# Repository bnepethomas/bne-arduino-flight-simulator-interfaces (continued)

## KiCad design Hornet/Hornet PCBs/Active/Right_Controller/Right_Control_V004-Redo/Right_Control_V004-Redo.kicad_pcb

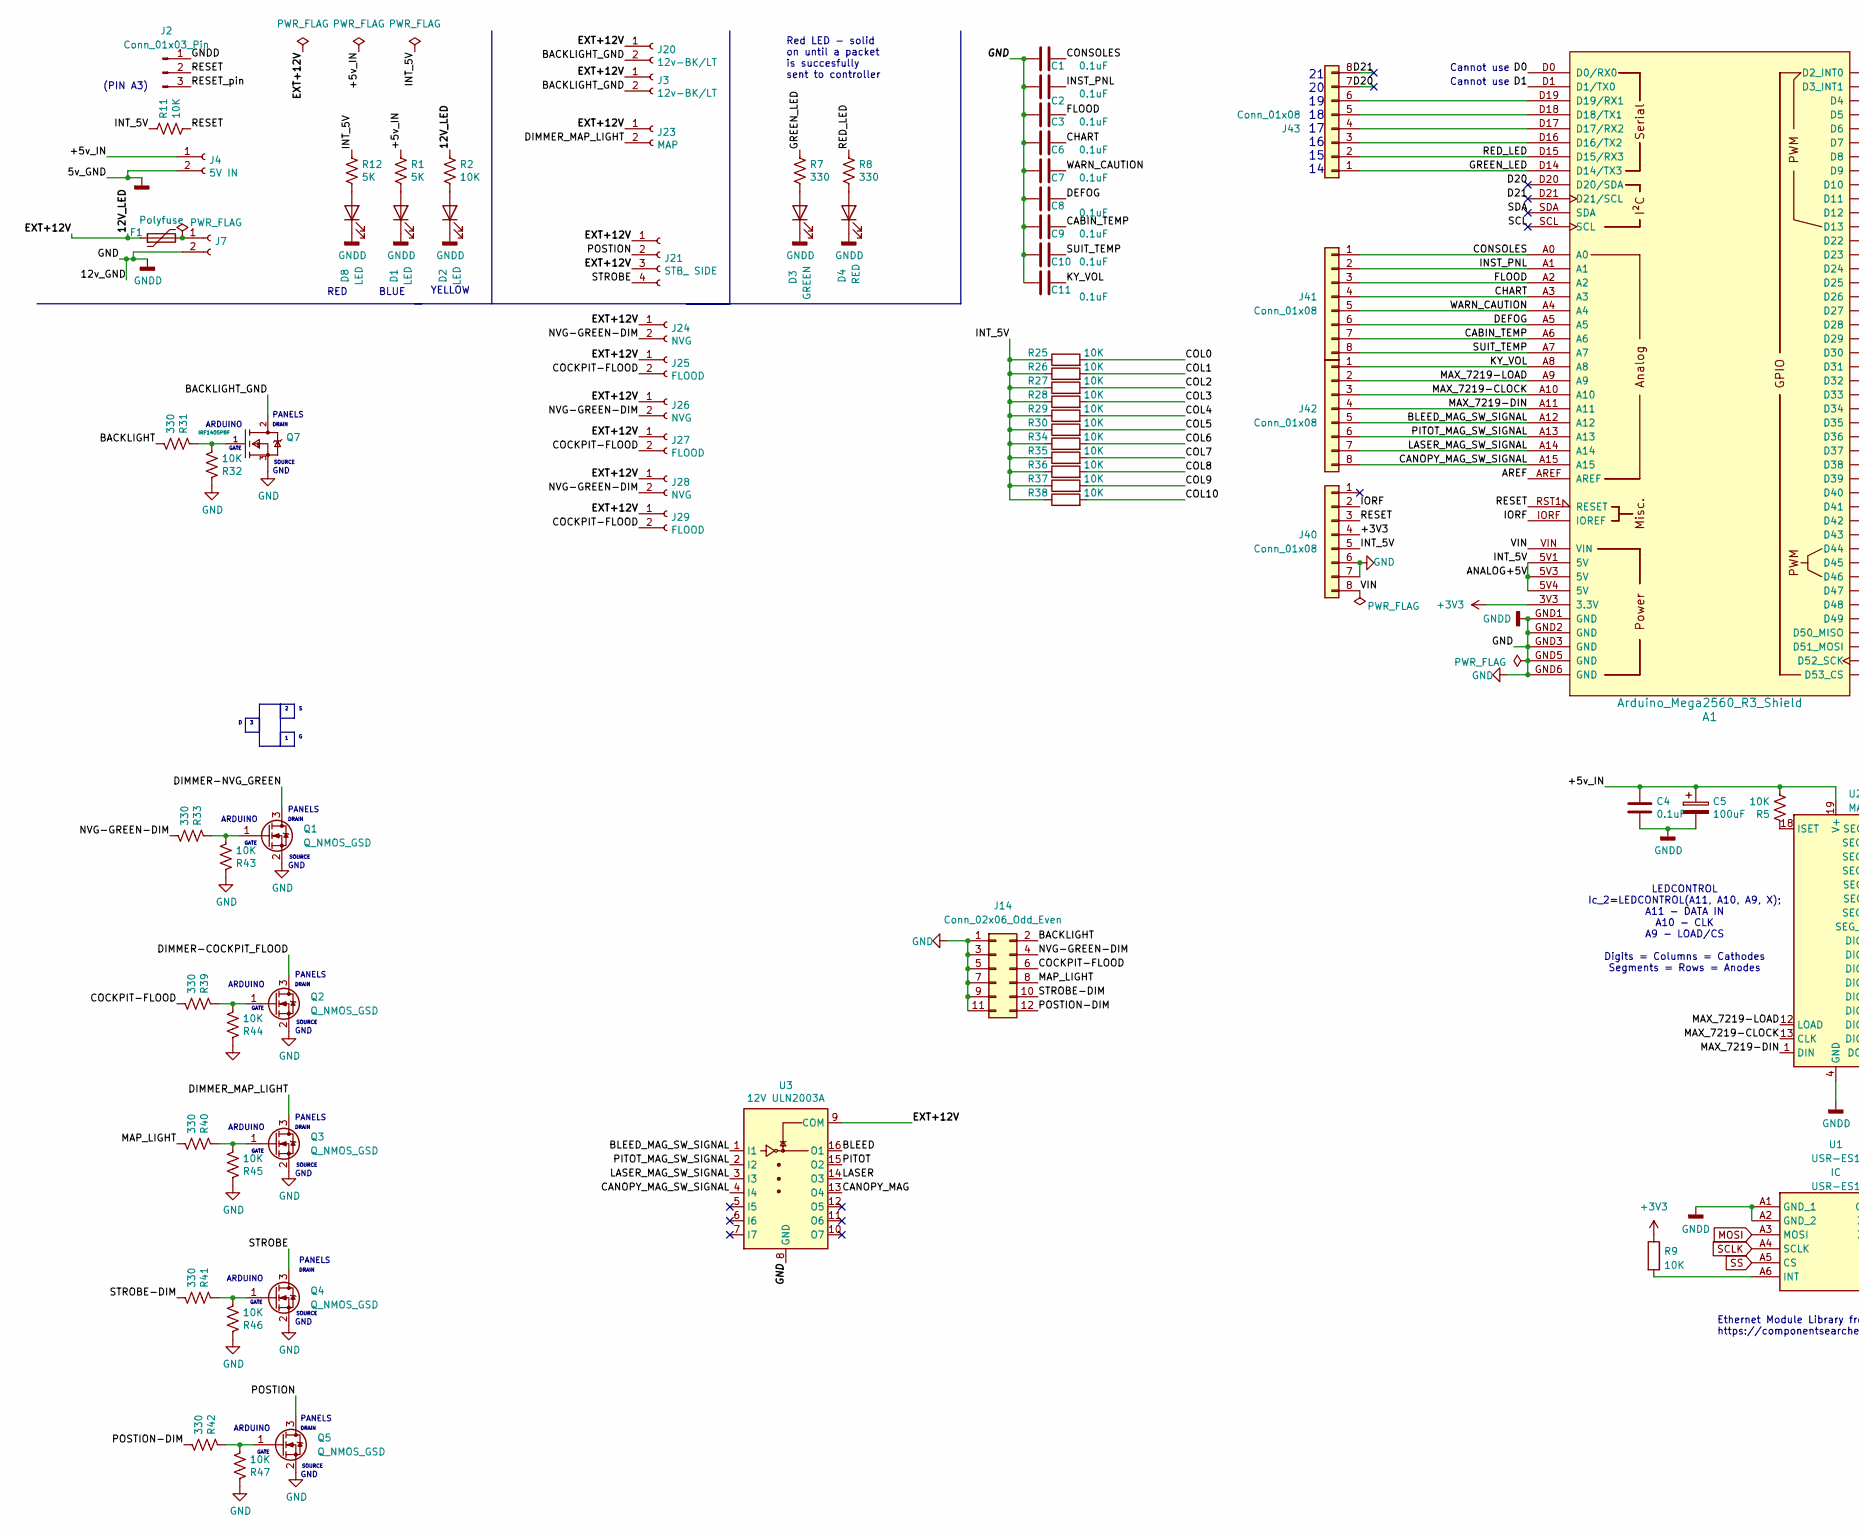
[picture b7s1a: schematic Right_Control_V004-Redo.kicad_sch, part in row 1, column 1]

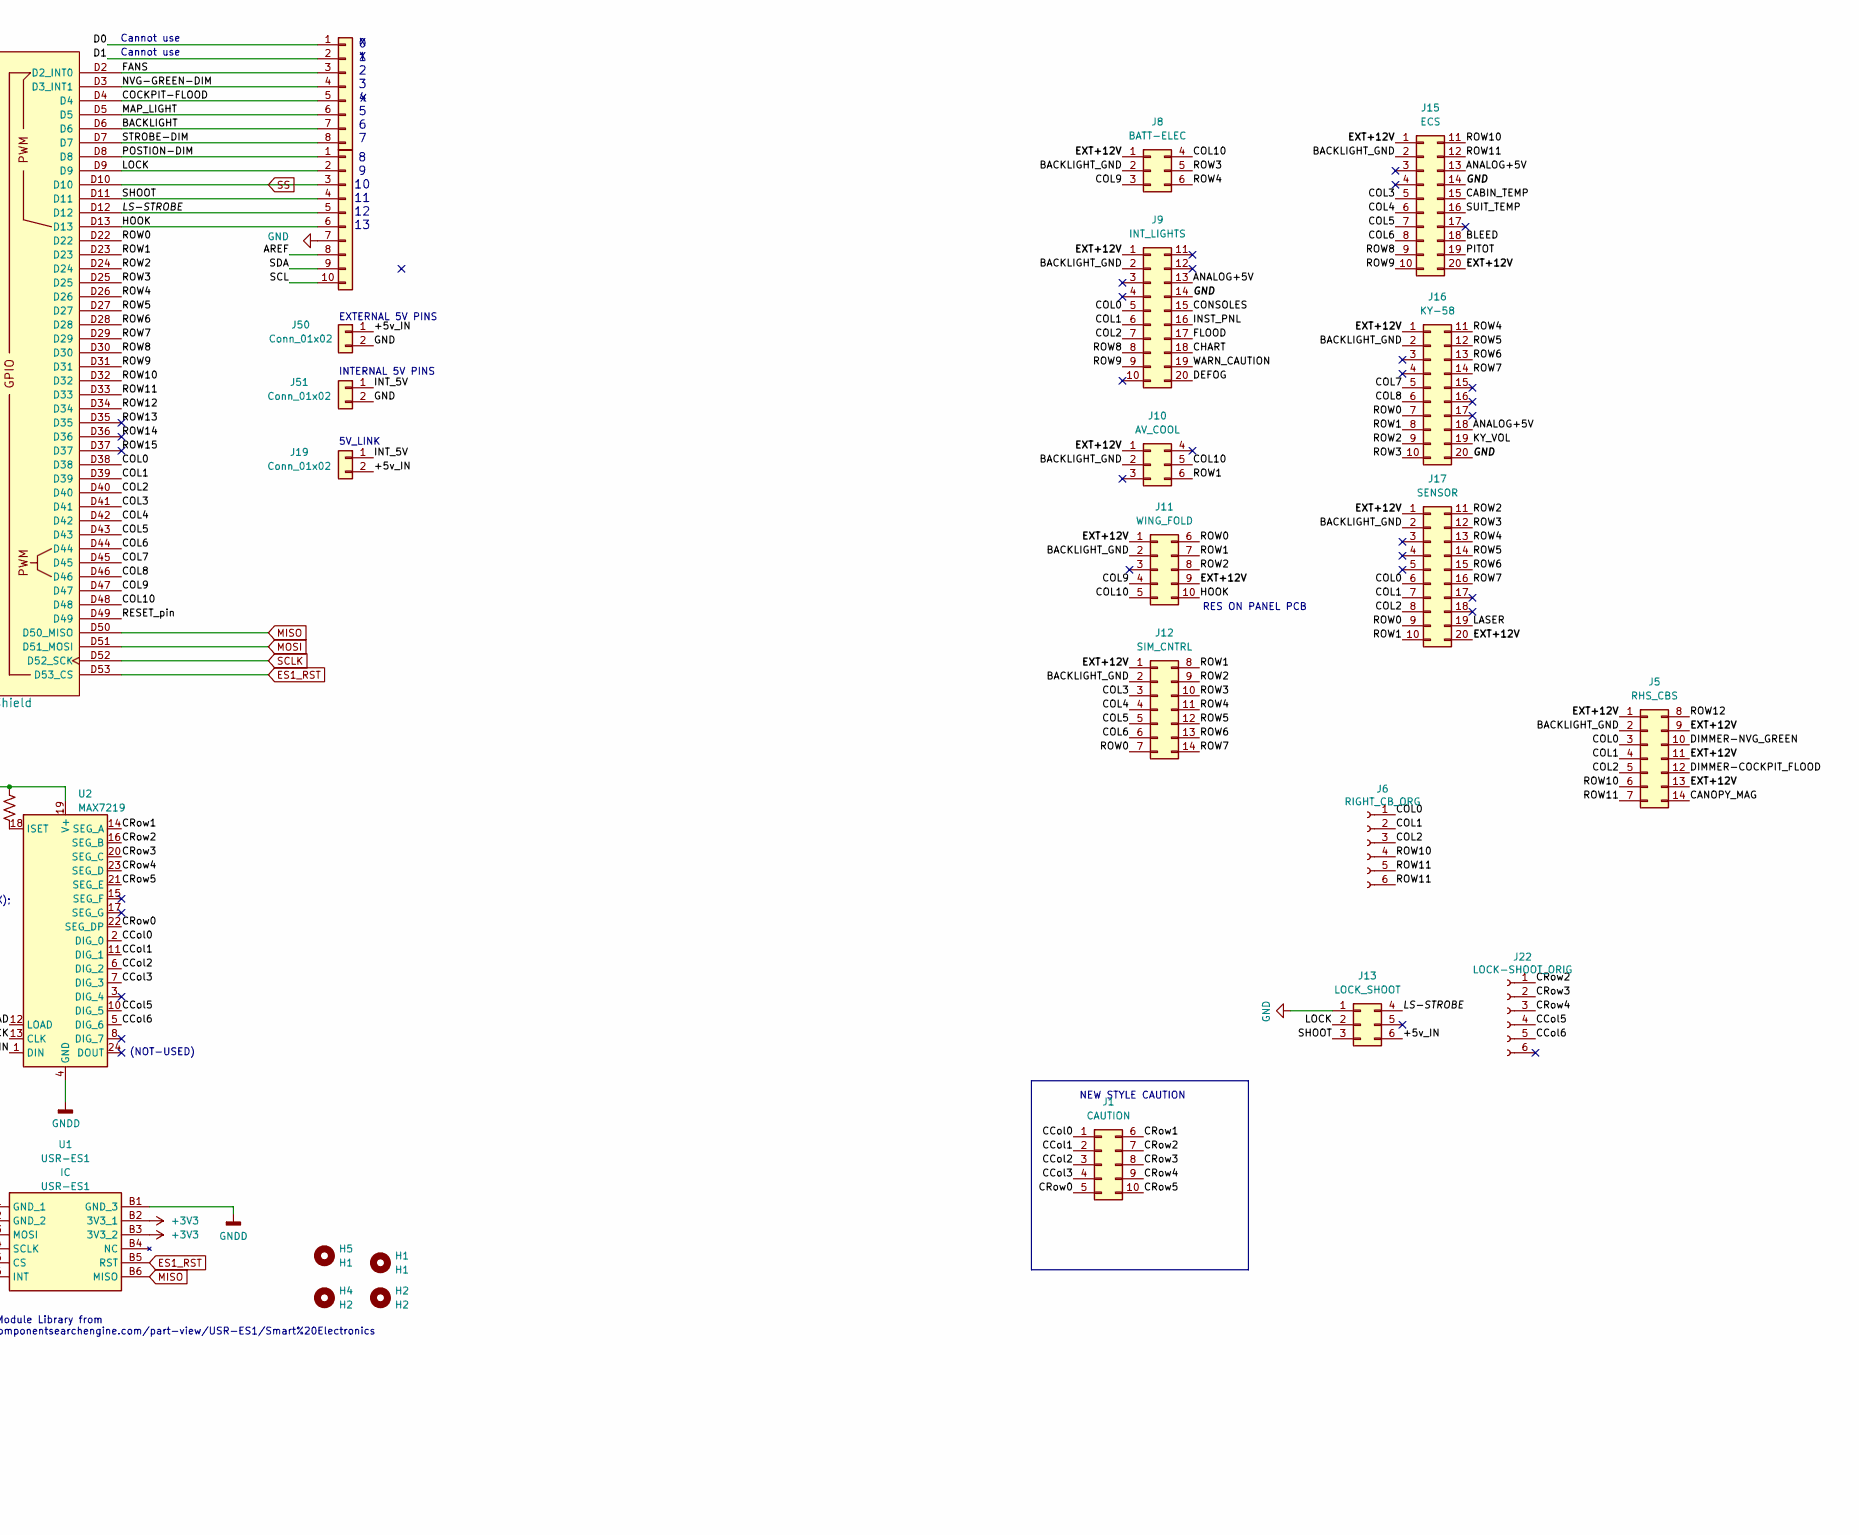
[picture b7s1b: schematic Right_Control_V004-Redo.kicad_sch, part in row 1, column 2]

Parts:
A1: Arduino_Mega2560_R3_Shield
C1, C2, C3, C4, C6, C7, C8, C9, C10, C11: 0.1uF; C_0805_2012Metric
C5: 100uF; C_1210_3225Metric
D1, D2, D8: LED; LED_0805_2012Metric
D3: GREEN; LED_0805_2012Metric
D4: RED; LED_0805_2012Metric
F1: Polyfuse; Fuse_1206_3216Metric
H1, H5: H1; MountingHole_2.5mm
H2, H4: H2; MountingHole_2.5mm
J1: CAUTION; IDC-Header_2x05_P2.54mm_Vertical
J2: Conn_01x03_Pin; PinHeader_1x03_P2.54mm_Vertical
J3, J20: 12v-BK/LT; Molex_KK-254_AE-6410-02A_1x02_P2.54mm_Vertical
J4: 5V IN; BarrelJack_Horizontal
J5: RHS_CBS; IDC-Header_2x07_P2.54mm_Vertical
J6: RIGHT_CB_ORG; Molex_KK-254_AE-6410-06A_1x06_P2.54mm_Vertical
J7: STEPPER IN 12-20VDC; BarrelJack_Horizontal
J8: BATT-ELEC; IDC-Header_2x03_P2.54mm_Vertical
J9: INT_LIGHTS; IDC-Header_2x10_P2.54mm_Vertical
J10: AV_COOL; IDC-Header_2x03_P2.54mm_Vertical
J11: WING_FOLD; IDC-Header_2x05_P2.54mm_Vertical
J12: SIM_CNTRL; IDC-Header_2x07_P2.54mm_Vertical
J13: LOCK_SHOOT; IDC-Header_2x03_P2.54mm_Vertical
J14: Conn_02x06_Odd_Even; PinHeader_2x06_P2.54mm_Vertical
J15: ECS; IDC-Header_2x10_P2.54mm_Vertical
J16: KY-58; IDC-Header_2x10_P2.54mm_Vertical
J17: SENSOR; IDC-Header_2x10_P2.54mm_Vertical
J19, J50, J51: Conn_01x02; PinHeader_1x02_P2.54mm_Vertical
J21: STB_ SIDE; Molex_KK-254_AE-6410-04A_1x04_P2.54mm_Vertical
J22: LOCK-SHOOT_ORIG; Molex_KK-254_AE-6410-06A_1x06_P2.54mm_Vertical
J23: MAP; Molex_KK-254_AE-6410-02A_1x02_P2.54mm_Vertical
J24, J26, J28: NVG; Molex_KK-254_AE-6410-02A_1x02_P2.54mm_Vertical
J25, J27, J29: FLOOD; Molex_KK-254_AE-6410-02A_1x02_P2.54mm_Vertical
J40, J41, J42, J43, J44: Conn_01x08; PinHeader_1x08_P2.54mm_Vertical
J45: Conn_01x10; PinHeader_1x10_P2.54mm_Vertical
Q1, Q2, Q3, Q4, Q5: Q_NMOS_GSD; SOT-23
Q7: IRF1405PBF; TO-220-3_Vertical; mouser part number 942-IRF1405PBF; digikey description MOSFET N-CH 55V 169A TO-220AB
R1, R12: 5K; R_0805_2012Metric
R2, R5, R9, R11, R25, R26, R27, R28, R29, R30, R32, R34, R35, R36, R37, R38, R43, R44, R45, R46, R47: 10K; R_0805_2012Metric
R7, R8, R31, R33, R39, R40, R41, R42: 330; R_0805_2012Metric
U1: USR-ES1; USRES1; Manufacturer_Part_Number USR-ES1
U2: MAX7219; DIP-24_W7.62mm_LongPads
U3: 12V ULN2003A; DIP-16_W7.62mm

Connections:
+3V3: A1.3V3 (3.3V), J40.4, R9.1, U1.B2 (3V3_1), U1.B3 (3V3_2)
/12V_LED: F1.1, J3.1, J5.1, J5.9, J5.11, J5.13, J8.1, J9.1, J10.1, J11.1, J11.9, J12.1, J15.1, J15.20, J16.1, J17.1, J17.20, J20.1, J21.1, J21.3, J23.1, J24.1, J25.1, J26.1, J27.1, J28.1, J29.1, R2.1, U3.9 (COM)
/+5v_IN: C4.1, C5.1, J4.1, J13.6, J19.2, J50.1, R1.1, R5.2, U2.19 (V+)
/ANALOG+5V: A1.5V1 (5V), A1.5V3 (5V), A1.5V4 (5V), J9.13, J15.13, J16.18, J19.1, J40.5, J51.1, R11.1, R12.1, R25.1, R26.1, R27.1, R28.1, R29.1, R30.1, R34.1, R35.1, R36.1, R37.1, R38.1
/AREF: A1.AREF, J45.8
/BACKLIGHT: A1.D6, J14.2, J44.7, R31.2
/BACKLIGHT_GND: J3.2, J5.2, J8.2, J9.2, J10.2, J11.2, J12.2, J15.2, J16.2, J17.2, J20.2, Q7.2 (D)
/BLEED: J15.18, U3.16 (O1)
/BLEED_MAG_SW_SIGNAL: A1.A12, J42.5, U3.1 (I1)
/CABIN_TEMP: A1.A6, C9.1, J15.15, J41.7
/CANOPY_MAG: J5.14, U3.13 (O4)
/CANOPY_MAG_SW_SIGNAL: A1.A15, J42.8, U3.4 (I4)
/CCol0: J1.1, U2.2 (DIG_0)
/CCol1: J1.2, U2.11 (DIG_1)
/CCol2: J1.3, U2.6 (DIG_2)
/CCol3: J1.4, U2.7 (DIG_3)
/CCol5: J22.4, U2.10 (DIG_5)
/CCol6: J22.5, U2.5 (DIG_6)
/CHART: A1.A3, C6.1, J9.18, J41.4
/COCKPIT-FLOOD: A1.D4, J14.6, J25.2, J27.2, J29.2, J44.5, R39.2
/COL0: A1.D38, J5.3, J6.1, J9.5, J17.6, R25.2
/COL1: A1.D39, J5.4, J6.2, J9.6, J17.7, R26.2
/COL2: A1.D40, J5.5, J6.3, J9.7, J17.8, R27.2
/COL3: A1.D41, J12.3, J15.5, R28.2
/COL4: A1.D42, J12.4, J15.6, R29.2
/COL5: A1.D43, J12.5, J15.7, R30.2
/COL6: A1.D44, J12.6, J15.8, R34.2
/COL7: A1.D45, J16.5, R35.2
/COL8: A1.D46, J16.6, R36.2
/COL9: A1.D47, J8.3, J11.4, R37.2
/COL10: A1.D48, J8.4, J10.5, J11.5, R38.2
/CONSOLES: A1.A0, C1.1, J9.15, J41.1
/CRow0: J1.5, U2.22 (SEG_DP)
/CRow1: J1.6, U2.14 (SEG_A)
/CRow2: J1.7, J22.1, U2.16 (SEG_B)
/CRow3: J1.8, J22.2, U2.20 (SEG_C)
/CRow4: J1.9, J22.3, U2.23 (SEG_D)
/CRow5: J1.10, U2.21 (SEG_E)
/D0: A1.D0 (D0/RX0), J44.1
/D1: A1.D1 (D1/TX0), J44.2
/D20: A1.D20 (D20/SDA), J43.7
/D21: A1.D21 (D21/SCL), J43.8
/DEFOG: A1.A5, C8.1, J9.20, J41.6
/DIMMER-COCKPIT_FLOOD: J5.12, Q2.3 (D)
/DIMMER-NVG_GREEN: J5.10, Q1.3 (D)
/DIMMER_MAP_LIGHT: J23.2, Q3.3 (D)
/FANS: A1.D2 (D2_INT0), J44.3
/FLOOD: A1.A2, C3.1, J9.17, J41.3
/GREEN_LED: A1.D14 (D14/TX3), J43.1, R7.1
/HOOK: A1.D13, J11.10, J45.6
/INST_PNL: A1.A1, C2.1, J9.16, J41.2
/IORF: A1.IORF (IOREF), J40.2
/KY_VOL: A1.A8, C11.1, J16.19, J42.1
/LASER: J17.19, U3.14 (O3)
/LASER_MAG_SW_SIGNAL: A1.A14, J42.7, U3.3 (I3)
/LOCK: A1.D9, J13.2, J45.2
/LS-STROBE: A1.D12, J13.4, J45.5
/MAP_LIGHT: A1.D5, J14.8, J44.6, R40.2
/MAX_7219-CLOCK: A1.A10, J42.3, U2.13 (CLK)
/MAX_7219-DIN: A1.A11, J42.4, U2.1 (DIN)
/MAX_7219-LOAD: A1.A9, J42.2, U2.12 (LOAD)
/NVG-GREEN-DIM: A1.D3 (D3_INT1), J14.4, J24.2, J26.2, J28.2, J44.4, R33.2
/PITOT: J15.19, U3.15 (O2)
/PITOT_MAG_SW_SIGNAL: A1.A13, J42.6, U3.2 (I2)
/POSTION: J21.2, Q5.3 (D)
/POSTION-DIM: A1.D8, J14.12, J45.1, R42.2
/RED_LED: A1.D15 (D15/RX3), J43.2, R8.1
/RESET: A1.RST1 (RESET), J2.2, J40.3, R11.2
/RESET_pin: A1.D49, J2.3
/ROW0: A1.D22, J11.6, J12.7, J16.7, J17.9
/ROW1: A1.D23, J10.6, J11.7, J12.8, J16.8, J17.10
/ROW2: A1.D24, J11.8, J12.9, J16.9, J17.11
/ROW3: A1.D25, J8.5, J12.10, J16.10, J17.12
/ROW4: A1.D26, J8.6, J12.11, J16.11, J17.13
/ROW5: A1.D27, J12.12, J16.12, J17.14
/ROW6: A1.D28, J12.13, J16.13, J17.15
/ROW7: A1.D29, J12.14, J16.14, J17.16
/ROW8: A1.D30, J9.8, J15.9
/ROW9: A1.D31, J9.9, J15.10
/ROW10: A1.D32, J5.6, J6.4, J15.11
/ROW11: A1.D33, J5.7, J6.5, J6.6, J15.12
/ROW12: A1.D34, J5.8
/ROW13: A1.D35
/ROW14: A1.D36
/ROW15: A1.D37
/SCL: A1.SCL, J45.10
/SDA: A1.SDA, J45.9
/SHOOT: A1.D11, J13.3, J45.4
/STROBE: J21.4, Q4.3 (D)
/STROBE-DIM: A1.D7, J14.10, J44.8, R41.2
/SUIT_TEMP: A1.A7, C10.1, J15.16, J41.8
/VIN: A1.VIN, J40.8
/WARN_CAUTION: A1.A4, C7.1, J9.19, J41.5
ES1_RST: A1.D53 (D53_CS), U1.B5 (RST)
GND: A1.GND1 (GND), A1.GND2 (GND), A1.GND3 (GND), A1.GND5 (GND), A1.GND6 (GND), C1.2, C2.2, C3.2, C4.2, C5.2, C6.2, C7.2, C8.2, C9.2, C10.2, C11.2, D1.1 (K), D2.1 (K), D3.1 (K), D4.1 (K), D8.1 (K), J2.1, J4.2, J7.2, J9.14, J13.1, J14.1, J14.3, J14.5, J14.7, J14.9, J14.11, J15.14, J16.20, J40.6, J40.7, J45.7, J50.2, J51.2, Q1.2 (S), Q2.2 (S), Q3.2 (S), Q4.2 (S), Q5.2 (S), Q7.3 (S), R32.1, R43.1, R44.1, R45.1, R46.1, R47.1, U1.A1 (GND_1), U1.A2 (GND_2), U1.B1 (GND_3), U2.4 (GND), U2.9 (GND), U3.8 (GND)
MISO: A1.D50 (D50_MISO), U1.B6 (MISO)
MOSI: A1.D51 (D51_MOSI), U1.A3 (MOSI)
unnamed: A1.D16 (D16/TX2), J43.3
unnamed: A1.D17 (D17/RX2), J43.4
unnamed: A1.D18 (D18/TX1), J43.5
unnamed: A1.D19 (D19/RX1), J43.6
unnamed: D1.2 (A), R1.2
unnamed: D2.2 (A), R2.2
unnamed: D3.2 (A), R7.2
unnamed: D4.2 (A), R8.2
unnamed: D8.2 (A), R12.2
unnamed: F1.2, J7.1
unnamed: Q1.1 (G), R33.1, R43.2
unnamed: Q2.1 (G), R39.1, R44.2
unnamed: Q3.1 (G), R40.1, R45.2
unnamed: Q4.1 (G), R41.1, R46.2
unnamed: Q5.1 (G), R42.1, R47.2
unnamed: Q7.1 (G), R31.1, R32.2
unnamed: R9.2, U1.A6 (INT)
unnamed: R5.1, U2.18 (ISET)
SCLK: A1.D52 (D52_SCK), U1.A4 (SCLK)
SS: A1.D10, J45.3, U1.A5 (CS)

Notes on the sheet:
YELLOW
ARDUINO
SOURCE
GND
PANELS
DRAIN
BLUE
RES ON PANEL PCB
NEW STYLE CAUTION
INTERNAL 5V PINS
5V_LINK
Ethernet Module Library from https://componentsearchengine.com/part-view/USR-ES1/Smart%20Electronics
LEDCONTROL Ic_2=LEDCONTROL(A11, A10, A9, X); A11 - DATA IN A10 - CLK A9 - LOAD/CS Digits = Columns = Cathodes Segments = Rows = Anodes
GATE
Cannot use
RED
(PIN A3)
0 1 2 3 4 5 6 7
Red LED - solid on until a packet is succesfully sent to controller
(NOT-USED)
21 20 19 18 17 16 15 14
EXTERNAL 5V PINS
8 9 10 11 12 13

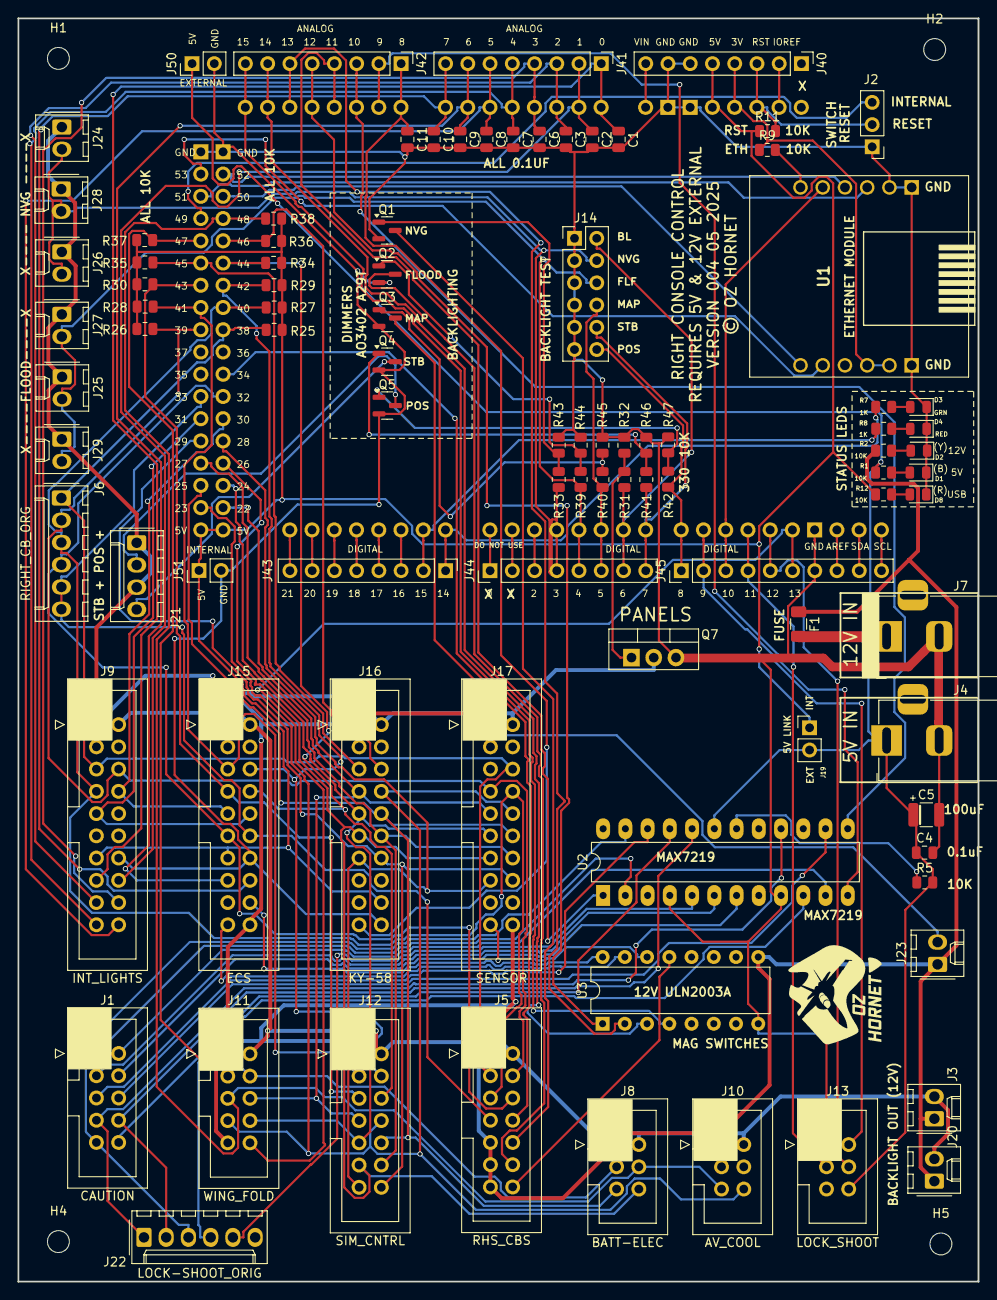
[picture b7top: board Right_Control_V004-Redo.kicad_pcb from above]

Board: 2 copper layers, 109.7 x 144.3 mm, 98 parts (0 on the bottom side), 114 nets.

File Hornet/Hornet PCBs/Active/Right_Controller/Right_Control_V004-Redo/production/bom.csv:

Designator,Footprint,Quantity,Value,LCSC Part #
A1,Arduino_Mega2560_R3_Shield,1,Arduino_Mega2560_R3_Shield,
"C1, C10, C11, C2, C3, C4, C6, C7, C8, C9",0805,10,0.1uF,
C5,1210,1,100uF,
"D1, D2, D8",0805,3,LED,
D3,0805,1,GREEN,
D4,0805,1,RED,
F1,1206,1,Polyfuse,
"H1, H5",MountingHole_2.5mm,2,H1,
"H2, H4",MountingHole_2.5mm,2,H2,
J1,IDC-Header_2x05_P2.54mm_Vertical,1,CAUTION,
J10,IDC-Header_2x03_P2.54mm_Vertical,1,AV_COOL,
J11,IDC-Header_2x05_P2.54mm_Vertical,1,WING_FOLD,
J12,IDC-Header_2x07_P2.54mm_Vertical,1,SIM_CNTRL,
J13,IDC-Header_2x03_P2.54mm_Vertical,1,LOCK_SHOOT,
J14,PinHeader_2x06_P2.54mm_Vertical,1,Conn_02x06_Odd_Even,
J15,IDC-Header_2x10_P2.54mm_Vertical,1,ECS,
J16,IDC-Header_2x10_P2.54mm_Vertical,1,KY-58,
J17,IDC-Header_2x10_P2.54mm_Vertical,1,SENSOR,
"J19, J50, J51",PinHeader_1x02_P2.54mm_Vertical,3,Conn_01x02,
J2,PinHeader_1x03_P2.54mm_Vertical,1,Conn_01x03_Pin,
"J20, J3",Molex_KK-254_AE-6410-02A_1x02_P2.54mm_Vertical,2,12v-BK/LT,
J21,Molex_KK-254_AE-6410-04A_1x04_P2.54mm_Vertical,1,STB_ SIDE,
J22,Molex_KK-254_AE-6410-06A_1x06_P2.54mm_Vertical,1,LOCK-SHOOT_ORIG,
J23,Molex_KK-254_AE-6410-02A_1x02_P2.54mm_Vertical,1,MAP,
"J24, J26, J28",Molex_KK-254_AE-6410-02A_1x02_P2.54mm_Vertical,3,NVG,
"J25, J27, J29",Molex_KK-254_AE-6410-02A_1x02_P2.54mm_Vertical,3,FLOOD,
J4,BarrelJack_Horizontal,1,5V IN,
"J40, J41, J42, J43, J44",PinHeader_1x08_P2.54mm_Vertical,5,Conn_01x08,
J45,PinHeader_1x10_P2.54mm_Vertical,1,Conn_01x10,
J5,IDC-Header_2x07_P2.54mm_Vertical,1,RHS_CBS,
J6,Molex_KK-254_AE-6410-06A_1x06_P2.54mm_Vertical,1,RIGHT_CB_ORG,
J7,BarrelJack_Horizontal,1,STEPPER IN 12-20VDC,
J8,IDC-Header_2x03_P2.54mm_Vertical,1,BATT-ELEC,
J9,IDC-Header_2x10_P2.54mm_Vertical,1,INT_LIGHTS,
"Q1, Q2, Q3, Q4, Q5",SOT-23,5,Q_NMOS_GSD,
Q7,TO-220-3_Vertical,1,IRF1405PBF,
"R1, R12",0805,2,5K,
"R11, R2, R25, R26, R27, R28, R29, R30, R32, R34, R35, R36, R37, R38, R43, R44, R45, R46, R47, R5, R9",0805,21,10K,
"R31, R33, R39, R40, R41, R42, R7, R8",0805,8,330,
U1,USRES1,1,USR-ES1,
U2,DIP-24_W7.62mm_LongPads,1,MAX7219,
U3,DIP-16_W7.62mm,1,12V ULN2003A,
